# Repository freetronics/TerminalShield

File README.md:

Freetronics Terminal Shield
===========================
Copyright 2011 Freetronics Pty Ltd  
Freetronics site:  <www.freetronics.com>  
Freetronics email: <info@freetronics.com>  

A general-purpose prototyping shield for the Arduino Uno, Freetronics
Eleven, and other compatible boards based on the same header format,
with handy screw terminals for connecting external wires.

Features:

 * Reset button wired through to Arduino reset pin.
 * Red, green, and blue general-purpose SMT LEDs with current-limiting
   resistors (drive HIGH to illuminate).
 * Blue "power on" LED with current-limiting resistor.
 * Large GND and 5V power rails alongside the prototyping area.
 * 2 x 100nF bypass/smoothing capacitors on supply rails.
 * Overlay guide where you need it: both top and bottom.

More information is available on our product page at:

  http://www.freetronics.com/terminalshield

The "docs" folder within this repository includes a handy copy of the
schematic in PDF format and image(s) of the pcb.

INSTALLATION
------------
The design is saved as an EAGLE project. EAGLE PCB design software is
available from www.cadsoftusa.com free for non-commercial use. To use
this project download it and place the directory containing these files
into the "eagle" directory on your computer. Then open EAGLE and
navigate to Projects -> eagle -> TerminalShield.

DISTRIBUTION
------------
The specific terms of distribution of this project are governed by the
license referenced below.

LICENSE
-------
Licensed under the TAPR Open Hardware License (www.tapr.org/OHL).
The "license" folder within this repository also contains a copy of
this license in plain text format.

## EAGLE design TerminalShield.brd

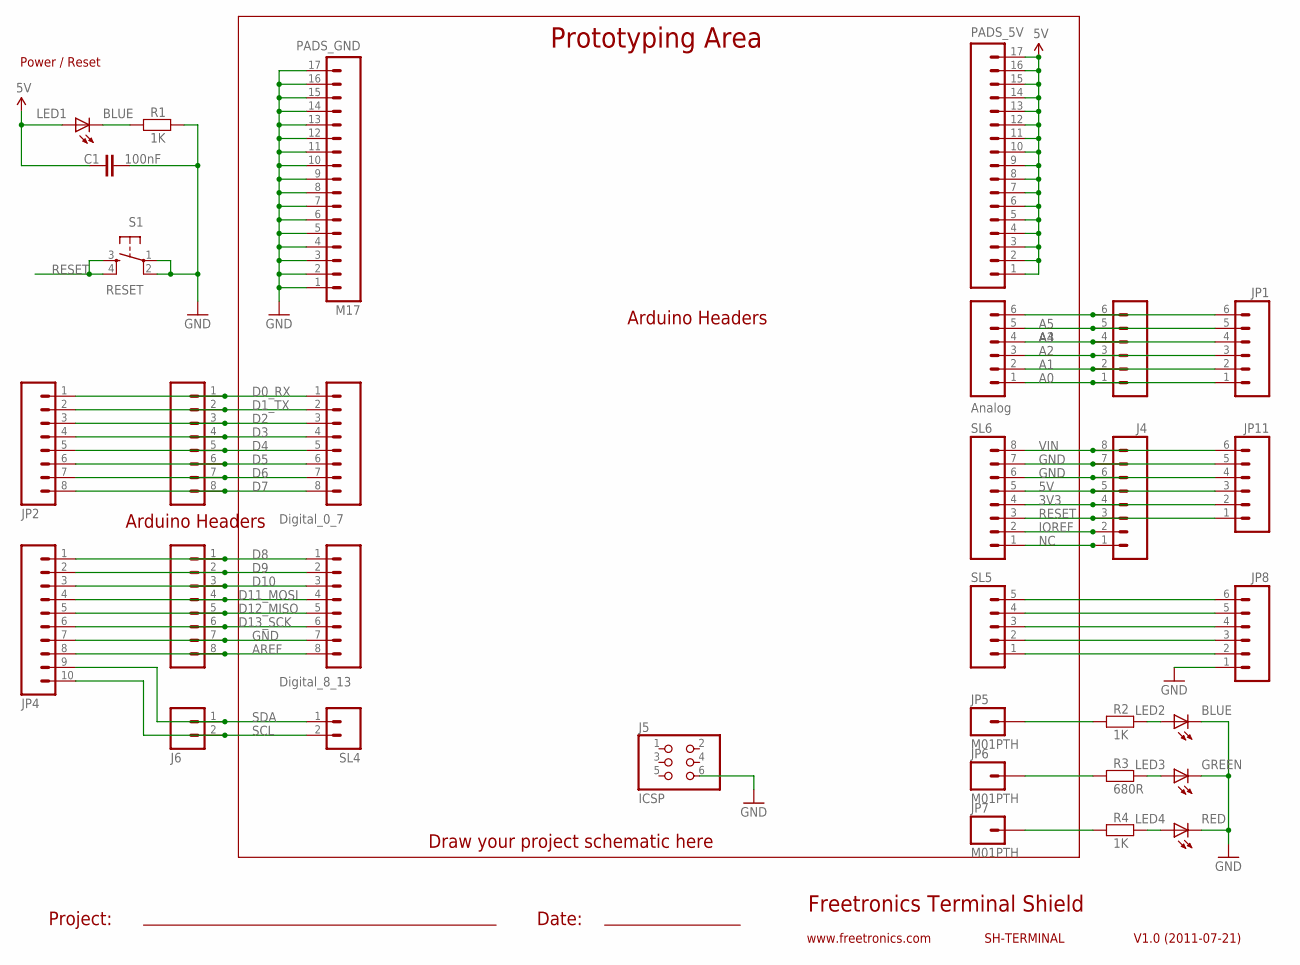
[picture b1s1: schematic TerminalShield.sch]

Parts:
C1: 100nF; 0603
J1: Analog; 1X06
J2: Digital_0_7; 1X08
J3: Digital_8_13; 1X08
J4: M08STD; 1X08
J5: ICSP; 2X03
J6: M02PTH; 1X02
JP1, JP8, JP11: M06; TERMINALBLOCK_3.5MM_6
JP2: M08; TERMINALBLOCK_3.5MM_8
JP4: M10; TERMINALBLOCK_3.5MM_10
JP5, JP6, JP7: M01PTH; 1X01
LED1, LED2: BLUE; LED-0603
LED3: GREEN; LED-0603
LED4: RED; LED-0603
PADS_5V: M17; 1X17
PADS_GND: M17; 1X17
R1, R2, R4: 1K; 0603
R3: 680R; 0603
S1: RESET; TACTILE_SWITCH_SMD
SL1: Analog; 1X06
SL2: Digital_0_7; 1X08
SL3: Digital_8_13; 1X08
SL4: M02PTH; 1X02
SL5: M05PTH; 1X05
SL6: M08STD; 1X08

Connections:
3V3: J4.4, JP11.2, SL6.4
5V: C1.1, J4.5, JP11.3, LED1.A, PADS_5V.1, PADS_5V.2, PADS_5V.3, PADS_5V.4, PADS_5V.5, PADS_5V.6, PADS_5V.7, PADS_5V.8, PADS_5V.9, PADS_5V.10, PADS_5V.11, PADS_5V.12, PADS_5V.13, PADS_5V.14, PADS_5V.15, PADS_5V.16, PADS_5V.17, SL6.5
A0: J1.1, JP1.1, SL1.1
A1: J1.2, JP1.2, SL1.2
A2: J1.3, JP1.3, SL1.3
A3: J1.4, JP1.4, SL1.4
A4: J1.5, JP1.5, SL1.5
A5: J1.6, JP1.6, SL1.6
AREF: J3.8, JP4.8, SL3.8
D0_RX: J2.1, JP2.1, SL2.1
D1_TX: J2.2, JP2.2, SL2.2
D2: J2.3, JP2.3, SL2.3
D3: J2.4, JP2.4, SL2.4
D4: J2.5, JP2.5, SL2.5
D5: J2.6, JP2.6, SL2.6
D6: J2.7, JP2.7, SL2.7
D7: J2.8, JP2.8, SL2.8
D8: J3.1, JP4.1, SL3.1
D9: J3.2, JP4.2, SL3.2
D10: J3.3, JP4.3, SL3.3
D11_MOSI: J3.4, JP4.4, SL3.4
D12_MISO: J3.5, JP4.5, SL3.5
D13_SCK: J3.6, JP4.6, SL3.6
GND: C1.2, J3.7, J4.6, J4.7, J5.6, JP4.7, JP8.1, JP11.4, JP11.5, LED2.C, LED3.C, LED4.C, PADS_GND.1, PADS_GND.2, PADS_GND.3, PADS_GND.4, PADS_GND.5, PADS_GND.6, PADS_GND.7, PADS_GND.8, PADS_GND.9, PADS_GND.10, PADS_GND.11, PADS_GND.12, PADS_GND.13, PADS_GND.14, PADS_GND.15, PADS_GND.16, PADS_GND.17, R1.2, S1.1, S1.2, SL3.7, SL6.6, SL6.7
IOREF: J4.2, SL6.2
unnamed: LED4.A, R4.2
unnamed: LED3.A, R3.2
unnamed: JP6.1, R3.1
unnamed: LED2.A, R2.2
unnamed: JP8.2, SL5.1
unnamed: JP8.3, SL5.2
unnamed: JP8.4, SL5.3
unnamed: JP8.5, SL5.4
unnamed: JP8.6, SL5.5
unnamed: LED1.C, R1.1
unnamed: JP5.1, R2.1
NC: J4.1, SL6.1
PADS_GND: JP7.1, R4.1
RESET: J4.3, JP11.1, S1.3, S1.4, SL6.3
SCL: J6.2, JP4.10, SL4.2
SDA: J6.1, JP4.9, SL4.1
VIN: J4.8, JP11.6, SL6.8

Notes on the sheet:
Prototyping Area
Freetronics Terminal Shield
V1.0 (2011-07-21)
www.freetronics.com
SH-TERMINAL
Power / Reset
Arduino Headers
Draw your project schematic here
Project:
Date:

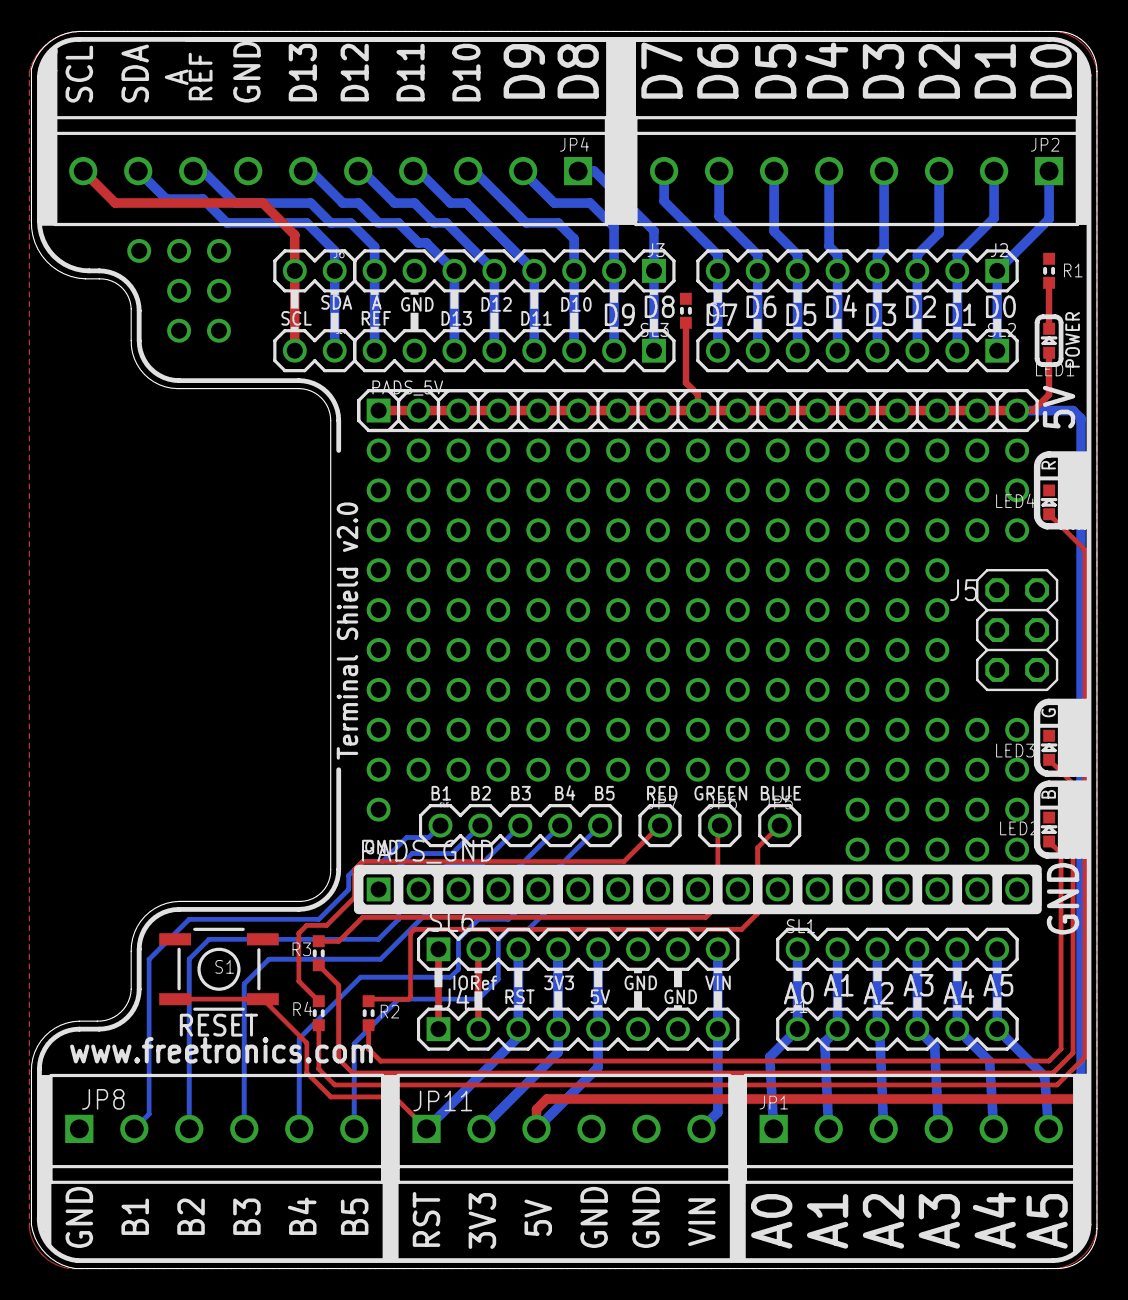
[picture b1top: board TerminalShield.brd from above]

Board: 2 copper layers, 67.8 x 78.7 mm, 32 parts (0 on the bottom side), 42 nets.

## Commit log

2011-08-29 Initial import
2011-08-29 Final production release
2014-06-23 Add gitignore
2014-06-26 Update schematic for R3
2014-07-03 TerminalShield v2.0 PCB (R3 compliant, ICSP, i2c on screw terminals, extra 5 pins of breakout screw terminals.)

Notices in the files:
TerminalShield.brd:
(c) 2014 Freetronics
